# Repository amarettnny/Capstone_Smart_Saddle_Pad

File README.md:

# Capstone_Smart_Saddle_Pad

## Setting up ESP-IDF for the first time

- This folder, along with its subfolders, contains the firmware that runs on the ESP32 microcontrollers using ESP-IDF. In order to compile and flash our ESP-IDF projects, you need to do the following:

    - Install the ESP-IDF extension on VS Code, and follow the ESP-IDF Setup to install the latest version of ESP-IDF (default parameters should be fine)
    - Open up the root folder of the ESP-IDF project in VS Code
    - Set the correct COM port, microcontroller, and ESP-IDF on the bottom left if necessary
    - Common Compilation Issues:
        - Make sure that the .vscode directory in the root folder of your project has a c_cpp_properties.json, launch.json, and a settings.json. If it is missing any of those, delete the .vscode folder, and have ESP-IDF generate it using the [Add .vscode subdirectoy files] button found by clicking on the ESP-IDF Explorer Icon in the Activity Bar and looking under Advanced.
        - Also see if deleting the build directory and rebuilding works as well.
        - Make sure that you configured the SDK to have the size of flash be 8MB for the XIAO ESP32C5. (change 2MB to 8 MB in CONFIG_ESPTOOLPY_FLASHSIZE_2MB=y)

- **Linux & MacOS: (OPTIONAL)**
    - Set up an alias to execute export.sh.
    - To locate your shell profile, run the following command:
      ```
      echo $Shell
      ```
    - for MacOS it should show:
      ```
      /bin/zsh
      ```
    - If so, then navigate to *~/.zshrc*, then copy-paste the alias code on the documentation (replace *esp-idf* with your directory name (should be *esp-idf-v5.5.2*))
    - When you create a new terminal, it will automatically use *~/.zshrc* to set environment variables. (Can also do ```source ~/.zshrc``` to re-run those variables)
    - Currently (as of 1/28/26): when you navigate to the esp-idf project, in your terminal, you will have to re-run:
      ```
      get_idf
      ```
    - Then you will be able to do ```idf.py``` commands within your terminal. See the official ESP32 Guide for more commands: https://docs.espressif.com/projects/esp-idf/en/latest/esp32/get-started/linux-macos-start-project.html

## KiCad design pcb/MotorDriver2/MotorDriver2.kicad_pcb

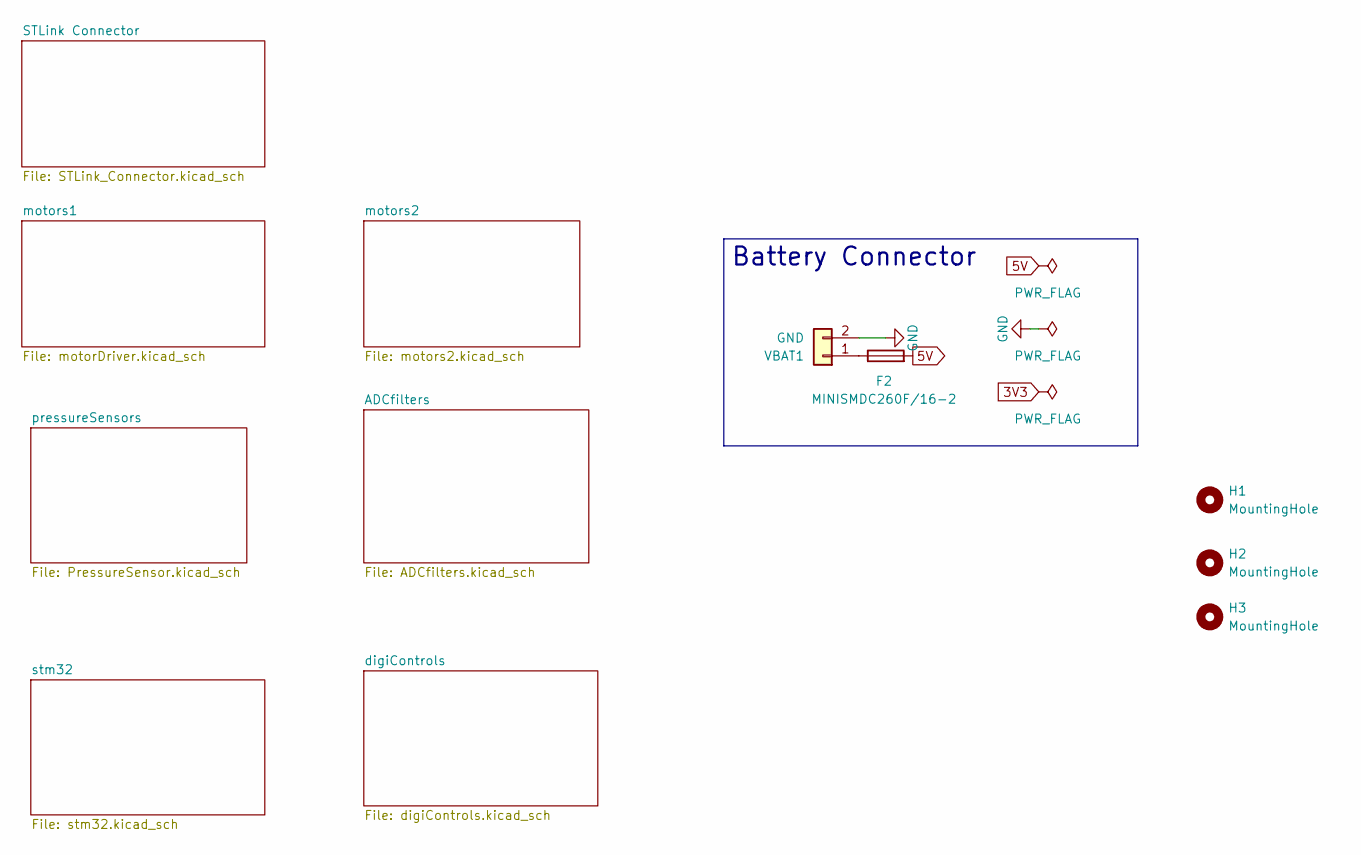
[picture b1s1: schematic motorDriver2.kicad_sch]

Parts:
F2: MINISMDC260F/16-2; Fuse_1812_4532Metric; LCSC C16490
H1, H2, H3: MountingHole; ToolingHole_1.152mm
VBAT1: GND; PinHeader_1x02_P2.54mm_Vertical

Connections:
5V: F2.2; also elsewhere on the board
GND: VBAT1.2; also elsewhere on the board
unnamed: F2.1, VBAT1.1

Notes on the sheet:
Battery Connector

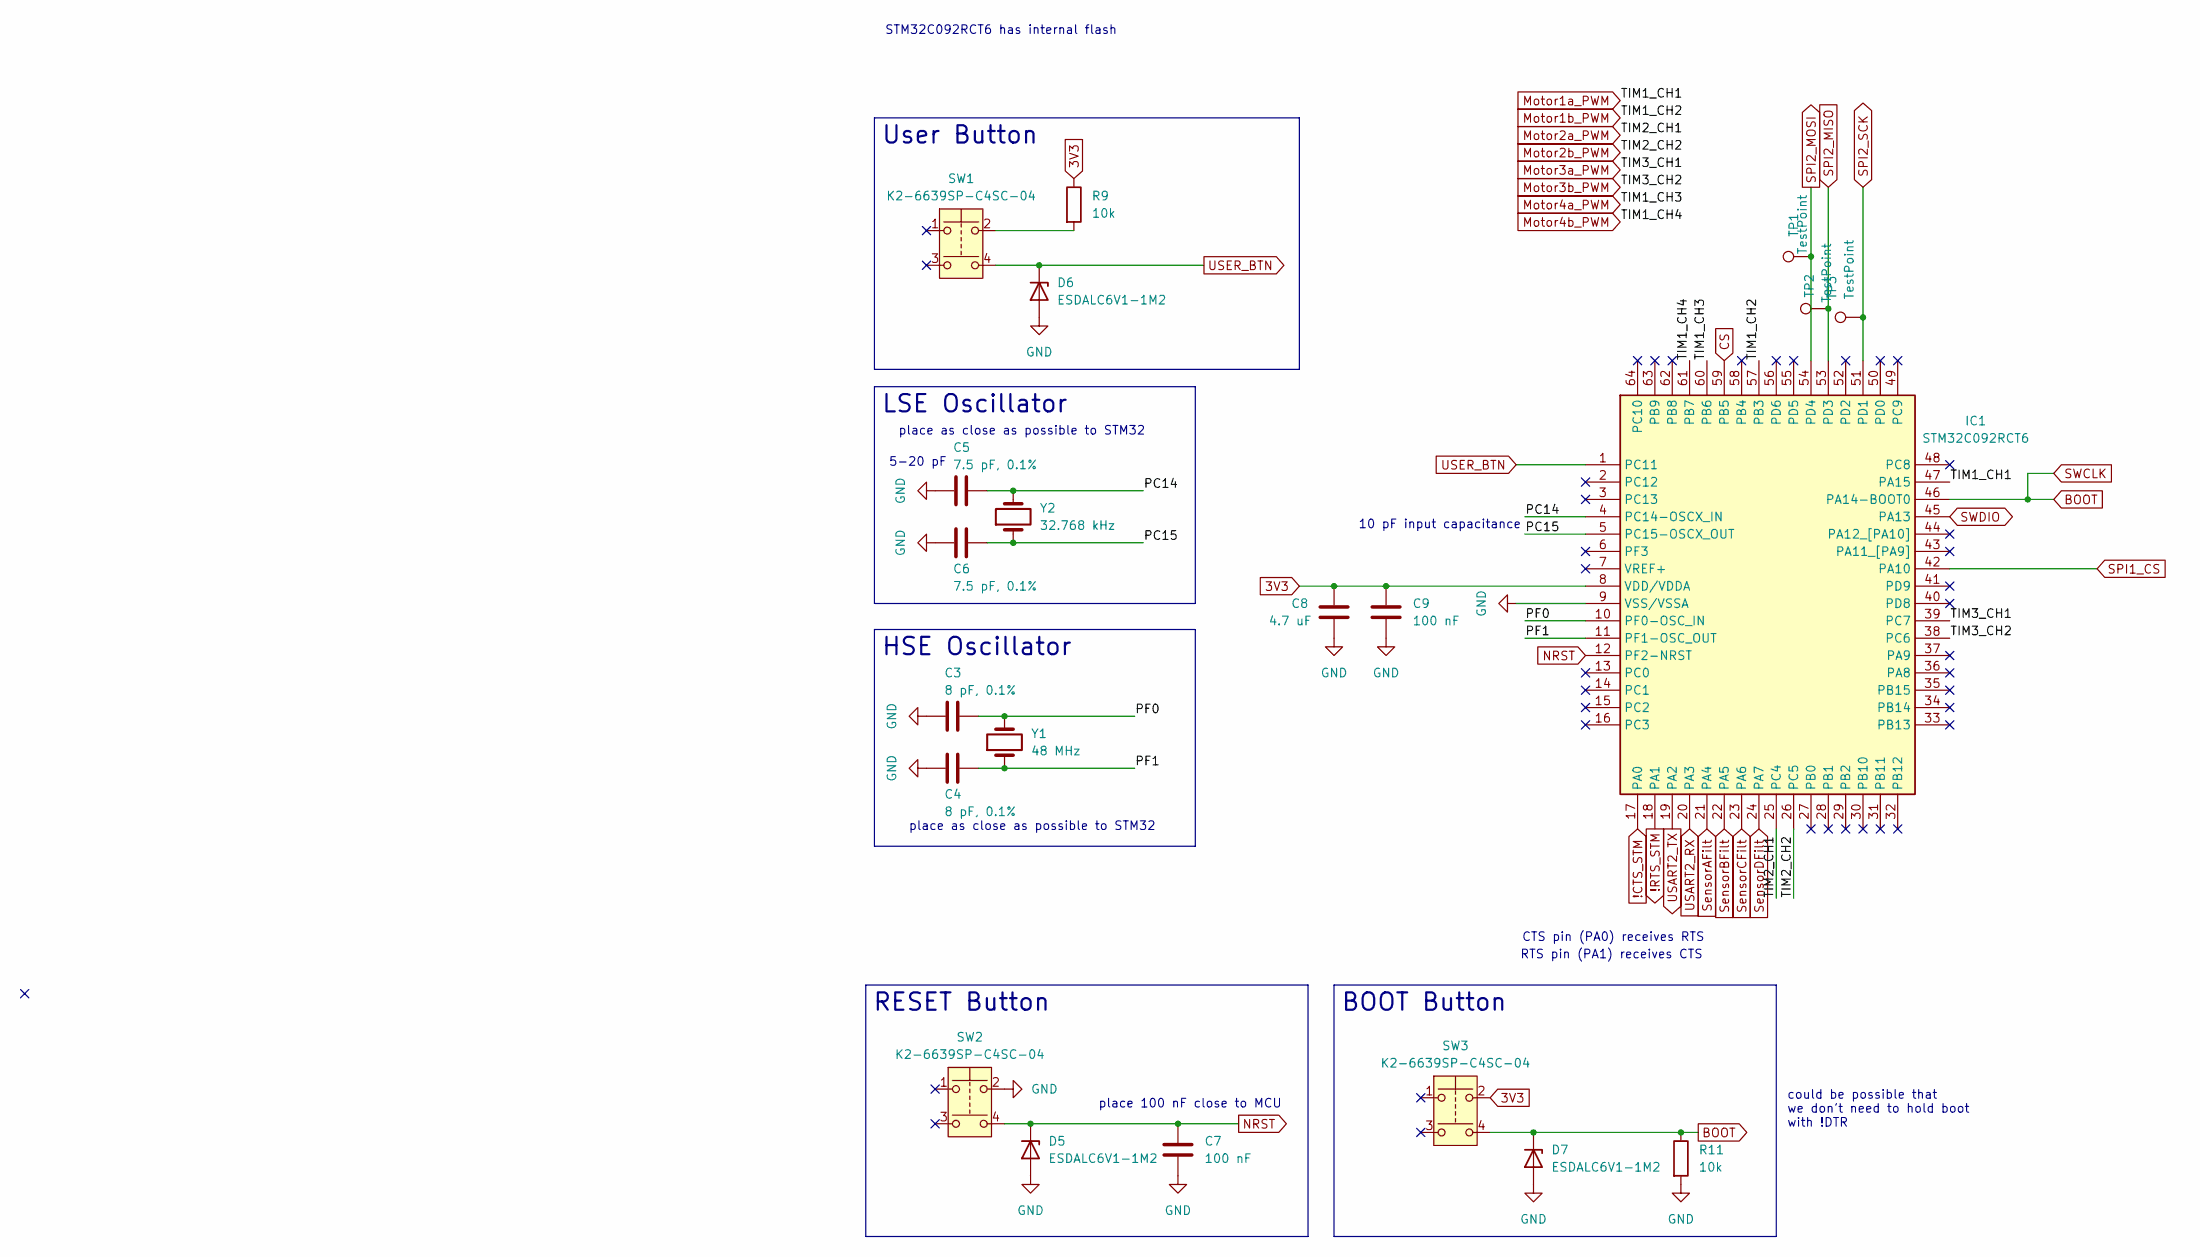
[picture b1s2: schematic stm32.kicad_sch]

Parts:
C3: 8 pF, 0.1%; C_0402_1005Metric; LCSC C3849295
C4: 8 pF, 0.1%; C_0402_1005Metric
C5, C6: 7.5 pF, 0.1%; C_0402_1005Metric; LCSC C161334
C7: 100 nF; C_0402_1005Metric; LCSC C1525
C8: 4.7 uF; C_0603_1608Metric; LCSC C19666
C9: 100 nF; C_0402_1005Metric
D5: ESDALC6V1-1M2; D_0402_1005Metric; LCSC C2649894
D6, D7: ESDALC6V1-1M2; D_0402_1005Metric
IC1: STM32C092RCT6; QFP50P1200X1200X160-64N; Manufacturer_Part_Number STM32C092RCT6; Mouser Part Number 511-STM32C092RCT6
R9, R11: 10k; R_0402_1005Metric
SW1, SW2, SW3: K2-6639SP-C4SC-04
TP1, TP2, TP3: TestPoint; TestPoint_Pad_1.0x1.0mm
Y1: 48 MHz; ECS-480-8-30-JGN-TR
Y2: 32.768 kHz; MU00527-32.768K

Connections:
3V3: C8.2, C9.1, IC1.8 (VDD/VDDA), R9.1, SW3.2; also elsewhere on the board
!CTS_STM: IC1.17 (PA0); also elsewhere on the board
!RTS_STM: IC1.18 (PA1); also elsewhere on the board
/stm32/PC14: C5.2, IC1.4 (PC14-OSCX_IN), Y2.2
/stm32/PC15: C6.1, IC1.5 (PC15-OSCX_OUT), Y2.1
/stm32/PF0: C3.2, IC1.10 (PF0-OSC_IN), Y1.2
/stm32/PF1: C4.1, IC1.11 (PF1-OSC_OUT), Y1.1
BOOT: D7.1 (K), IC1.46 (PA14-BOOT0), R11.1, SW3.4; also elsewhere on the board
CS: IC1.59 (PB5); also elsewhere on the board
GND: C3.1, C4.2, C5.1, C6.2, C7.2, C8.1, C9.2, D5.2 (A), D6.2 (A), D7.2 (A), IC1.9 (VSS/VSSA), R11.2, SW2.2; also elsewhere on the board
Motor1a_PWM: IC1.47 (PA15); also elsewhere on the board
Motor1b_PWM: IC1.57 (PB3); also elsewhere on the board
Motor2a_PWM: IC1.25 (PC4); also elsewhere on the board
Motor2b_PWM: IC1.26 (PC5); also elsewhere on the board
Motor3a_PWM: IC1.39 (PC7); also elsewhere on the board
Motor3b_PWM: IC1.38 (PC6); also elsewhere on the board
Motor4a_PWM: IC1.60 (PB6); also elsewhere on the board
Motor4b_PWM: IC1.61 (PB7); also elsewhere on the board
NRST: C7.1, D5.1 (K), IC1.12 (PF2-NRST), SW2.4
unnamed: R9.2, SW1.2
SPI1_CS: IC1.42 (PA10)
SPI2_MISO: IC1.53 (PD3), TP2.1; also elsewhere on the board
SPI2_MOSI: IC1.54 (PD4), TP1.1; also elsewhere on the board
SPI2_SCK: IC1.51 (PD1), TP3.1; also elsewhere on the board
SWDIO: IC1.45 (PA13); also elsewhere on the board
SensorAFilt: IC1.21 (PA4); also elsewhere on the board
SensorBFilt: IC1.22 (PA5); also elsewhere on the board
SensorCFilt: IC1.23 (PA6); also elsewhere on the board
SensorDFilt: IC1.24 (PA7); also elsewhere on the board
USART2_RX: IC1.20 (PA3); also elsewhere on the board
USART2_TX: IC1.19 (PA2); also elsewhere on the board
USER_BTN: D6.1 (K), IC1.1 (PC11), SW1.4

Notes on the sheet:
CTS pin (PA0) receives RTS
10 pF input capacitance
place as close as possible to STM32
5-20 pF
STM32C092RCT6 has internal flash
place 100 nF close to MCU
could be possible that we don't need to hold boot with !DTR
RTS pin (PA1) receives CTS
RESET Button
User Button
BOOT Button
HSE Oscillator
LSE Oscillator

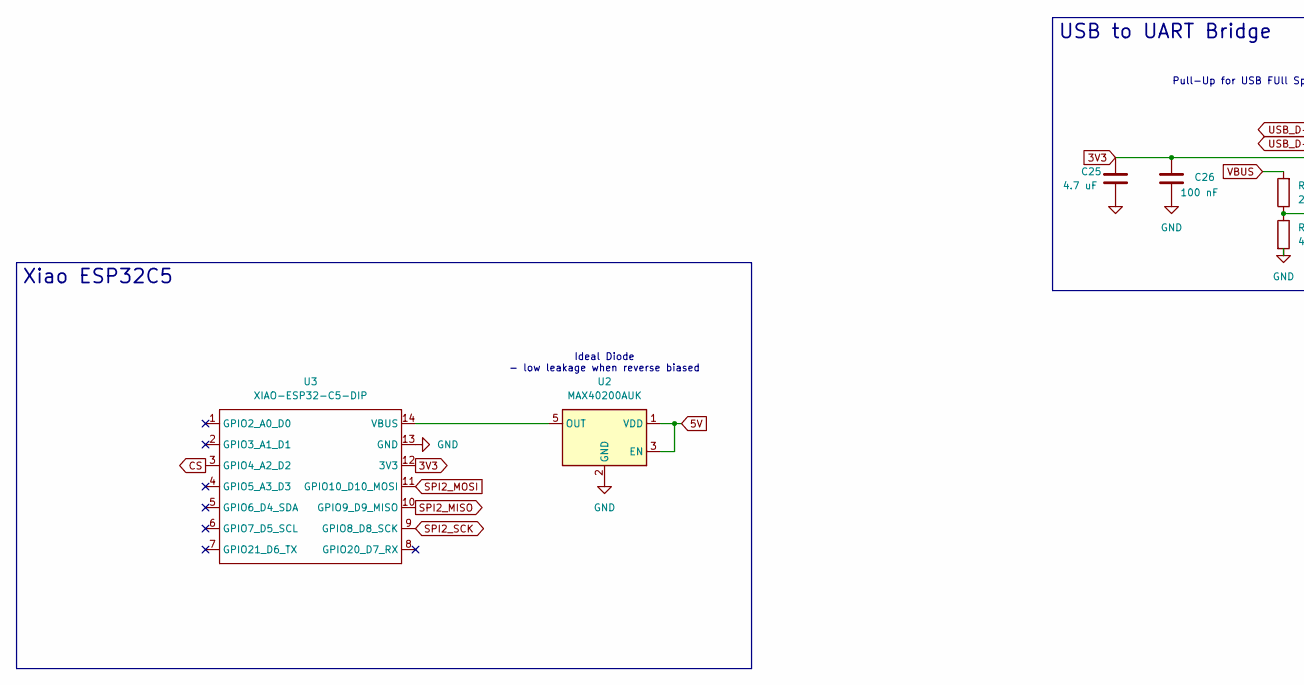
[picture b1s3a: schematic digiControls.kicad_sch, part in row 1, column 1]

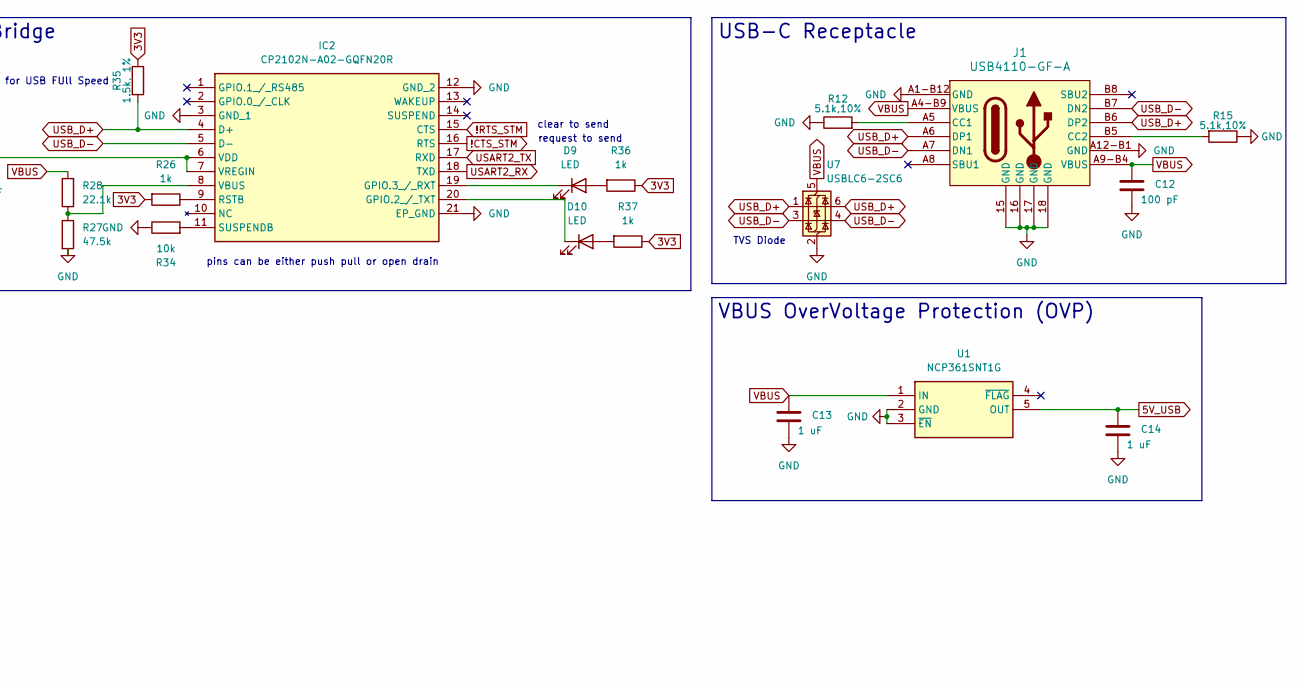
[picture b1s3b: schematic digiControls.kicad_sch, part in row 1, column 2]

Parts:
C12: 100 pF; C_0402_1005Metric
C13, C14: 1 uF; C_0603_1608Metric; LCSC C15849
C25: 4.7 uF; C_0603_1608Metric
C26: 100 nF; C_0402_1005Metric
D9, D10: LED; D_0402_1005Metric
IC2: CP2102N-A02-GQFN20R; CP2102NA02GQFN20; Mouser Part Number 634-CP2102NA02QFN20R
J1: USB4110-GF-A; USB4110-GF-A_GCT
R12, R15: 5.1k,10%; R_0402_1005Metric; LCSC C25905
R26, R36, R37: 1k; R_0402_1005Metric
R27: 47.5k; R_0402_1005Metric
R28: 22.1k; R_0402_1005Metric
R34: 10k; R_0402_1005Metric
R35: 1.5k, 1%; R_0402_1005Metric
U1: NCP361SNT1G; SOT95P275X110-5N; Mouser Part Number 863-NCP361SNT1G
U2: MAX40200AUK; SOT-23-5
U3: XIAO-ESP32-C5-DIP
U7: USBLC6-2SC6; SOT-23-6

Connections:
3V3: C25.2, C26.2, IC2.6 (VDD), IC2.7 (VREGIN), R26.2, R35.1, R36.1, R37.1, U3.12 (3V3); also elsewhere on the board
5V: U2.1 (VDD), U2.3 (EN); also elsewhere on the board
5V_USB: C14.2, U1.5 (OUT)
!CTS_STM: IC2.16 (RTS); also elsewhere on the board
!RTS_STM: IC2.15 (CTS); also elsewhere on the board
CS: U3.3 (GPIO4_A2_D2); also elsewhere on the board
GND: C12.1, C13.1, C14.1, C25.1, C26.1, IC2.3 (GND_1), IC2.12 (GND_2), IC2.21 (EP_GND), J1.15 (GND), J1.16 (GND), J1.17 (GND), J1.18 (GND), J1.A1-B12 (GND), J1.A12-B1 (GND), R12.1, R15.1, R27.2, R34.1, U1.2 (GND), U1.3 (~EN), U2.2 (GND), U3.13 (GND), U7.2 (GND); also elsewhere on the board
unnamed: D9.2 (A), R36.2
unnamed: D9.1 (K), IC2.19 (GPIO.3_/_RXT)
unnamed: D10.2 (A), R37.2
unnamed: D10.1 (K), IC2.20 (GPIO.2_/_TXT)
unnamed: IC2.9 (RSTB), R26.1
unnamed: IC2.11 (SUSPENDB), R34.2
unnamed: IC2.8 (VBUS), R27.1, R28.1
unnamed: J1.A5 (CC1), R12.2
unnamed: J1.B5 (CC2), R15.2
unnamed: U2.5 (OUT), U3.14 (VBUS)
SPI2_MISO: U3.10 (GPIO9_D9_MISO); also elsewhere on the board
SPI2_MOSI: U3.11 (GPIO10_D10_MOSI); also elsewhere on the board
SPI2_SCK: U3.9 (GPIO8_D8_SCK); also elsewhere on the board
USART2_RX: IC2.18 (TXD); also elsewhere on the board
USART2_TX: IC2.17 (RXD); also elsewhere on the board
USB_D+: IC2.4 (D+), J1.A6 (DP1), J1.B6 (DP2), R35.2, U7.1 (I/O1), U7.6 (I/O1)
USB_D-: IC2.5 (D-), J1.A7 (DN1), J1.B7 (DN2), U7.3 (I/O2), U7.4 (I/O2)
VBUS: C12.2, C13.2, J1.A4-B9 (VBUS), J1.A9-B4 (VBUS), R28.2, U1.1 (IN), U7.5 (VBUS)

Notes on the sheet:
TVS Diode
request to send
Ideal Diode - low leakage when reverse biased
pins can be either push pull or open drain
clear to send
Pull-Up for USB FUll Speed
VBUS OverVoltage Protection (OVP)
USB to UART Bridge
Xiao ESP32C5
USB-C Receptacle

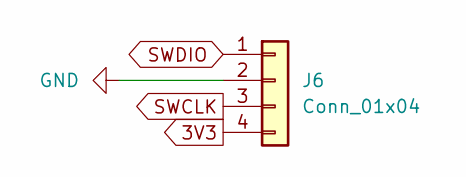
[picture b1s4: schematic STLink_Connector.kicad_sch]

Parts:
J6: Conn_01x04; PinHeader_1x04_P2.54mm_Vertical

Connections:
3V3: J6.4; also elsewhere on the board
BOOT: J6.3; also elsewhere on the board
GND: J6.2; also elsewhere on the board
SWDIO: J6.1; also elsewhere on the board

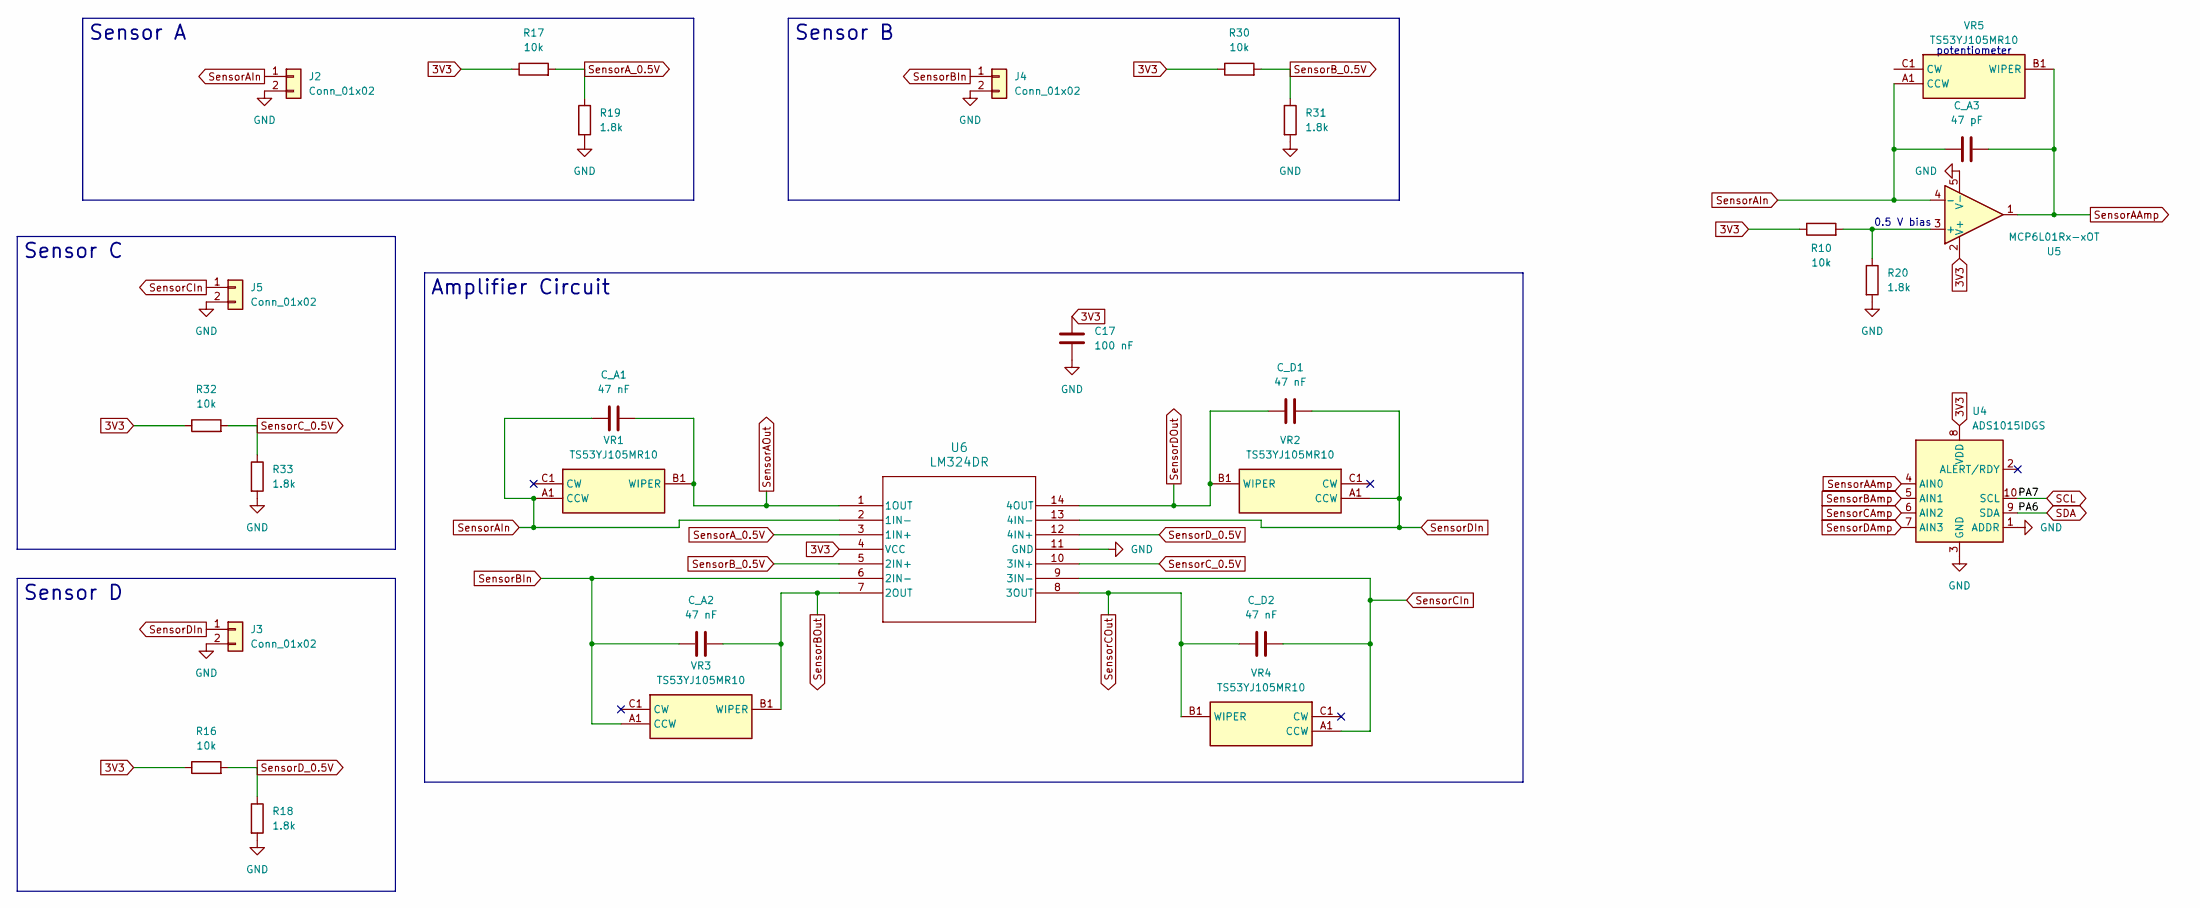
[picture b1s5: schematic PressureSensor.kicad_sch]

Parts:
C17: 100 nF; C_0402_1005Metric
C_A1: 47 nF; C_0402_1005Metric; LCSC C77012
C_A2: 47 nF; C_0402_1005Metric
C_A3: 47 pF; C_0402_1005Metric; LCSC C77012
C_D1, C_D2: 47 nF; C_0402_1005Metric
J2, J3, J4, J5: Conn_01x02; PinHeader_1x02_P2.54mm_Vertical
R10, R16, R17, R30, R32: 10k; R_0402_1005Metric
R18, R19: 1.8k; R_0402_1005Metric; LCSC C25871
R20, R31, R33: 1.8k; R_0402_1005Metric
U4: ADS1015IDGS; TSSOP-10_3x3mm_P0.5mm
U5: MCP6L01Rx-xOT; SOT-23-5
U6: LM324DR; D14
VR1, VR2, VR3, VR4, VR5: TS53YJ105MR10; Mouser Part Number 72-TS53YJ-1M

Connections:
3V3: C17.1, R10.1, R16.1, R17.1, R30.1, R32.1, U4.8 (VDD), U5.2 (V+), U6.4 (VCC); also elsewhere on the board
GND: C17.2, J2.2, J3.2, J4.2, J5.2, R18.2, R19.2, R20.2, R31.2, R33.2, U4.1 (ADDR), U4.3 (GND), U5.5 (V-), U6.11 (GND); also elsewhere on the board
unnamed: C_A3.1, U4.4 (AIN0), U5.1, VR5.B1 (WIPER)
unnamed: R10.2, R20.1, U5.3 (+)
SensorAIn: C_A1.2, C_A3.2, J2.1, U5.4 (-), U6.2 (1IN-), VR1.A1 (CCW), VR5.A1 (CCW)
SensorAOut: C_A1.1, U6.1 (1OUT), VR1.B1 (WIPER); also elsewhere on the board
SensorA_0.5V: R17.2, R19.1, U6.3 (1IN+)
SensorBIn: C_A2.2, J4.1, U6.6 (2IN-), VR3.A1 (CCW)
SensorBOut: C_A2.1, U6.7 (2OUT), VR3.B1 (WIPER); also elsewhere on the board
SensorB_0.5V: R30.2, R31.1, U6.5 (2IN+)
SensorCIn: C_D2.1, J5.1, U6.9 (3IN-), VR4.A1 (CCW)
SensorCOut: C_D2.2, U6.8 (3OUT), VR4.B1 (WIPER); also elsewhere on the board
SensorC_0.5V: R32.2, R33.1, U6.10 (3IN+)
SensorDIn: C_D1.1, J3.1, U6.13 (4IN-), VR2.A1 (CCW)
SensorDOut: C_D1.2, U6.14 (4OUT), VR2.B1 (WIPER); also elsewhere on the board
SensorD_0.5V: R16.2, R18.1, U6.12 (4IN+)

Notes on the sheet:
potentiometer
0.5 V bias
Amplifier Circuit
Sensor B
Sensor D
Sensor C
Sensor A

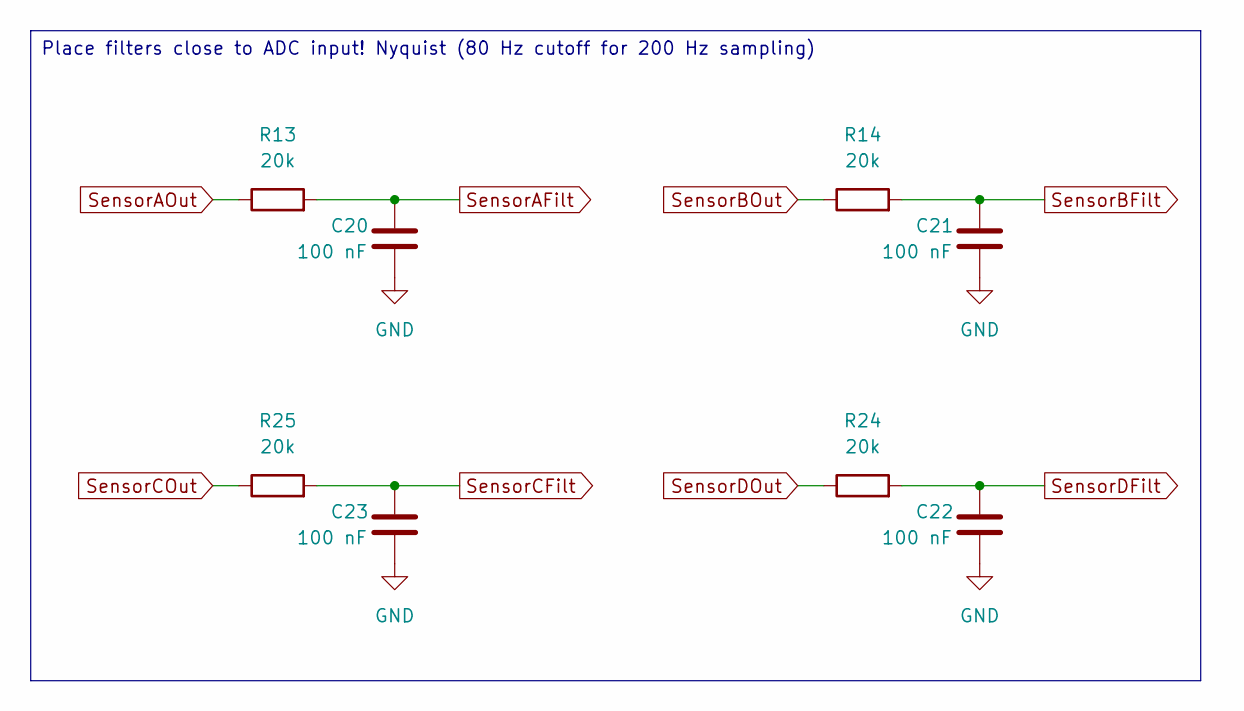
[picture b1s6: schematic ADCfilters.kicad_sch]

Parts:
C20, C21, C22, C23: 100 nF; C_0402_1005Metric
R13, R14, R24, R25: 20k; R_0402_1005Metric

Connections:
GND: C20.1, C21.1, C22.1, C23.1; also elsewhere on the board
SensorAFilt: C20.2, R13.2; also elsewhere on the board
SensorAOut: R13.1; also elsewhere on the board
SensorBFilt: C21.2, R14.2; also elsewhere on the board
SensorBOut: R14.1; also elsewhere on the board
SensorCFilt: C23.2, R25.2; also elsewhere on the board
SensorCOut: R25.1; also elsewhere on the board
SensorDFilt: C22.2, R24.2; also elsewhere on the board
SensorDOut: R24.1; also elsewhere on the board

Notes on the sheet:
Place filters close to ADC input! Nyquist (80 Hz cutoff for 200 Hz sampling)

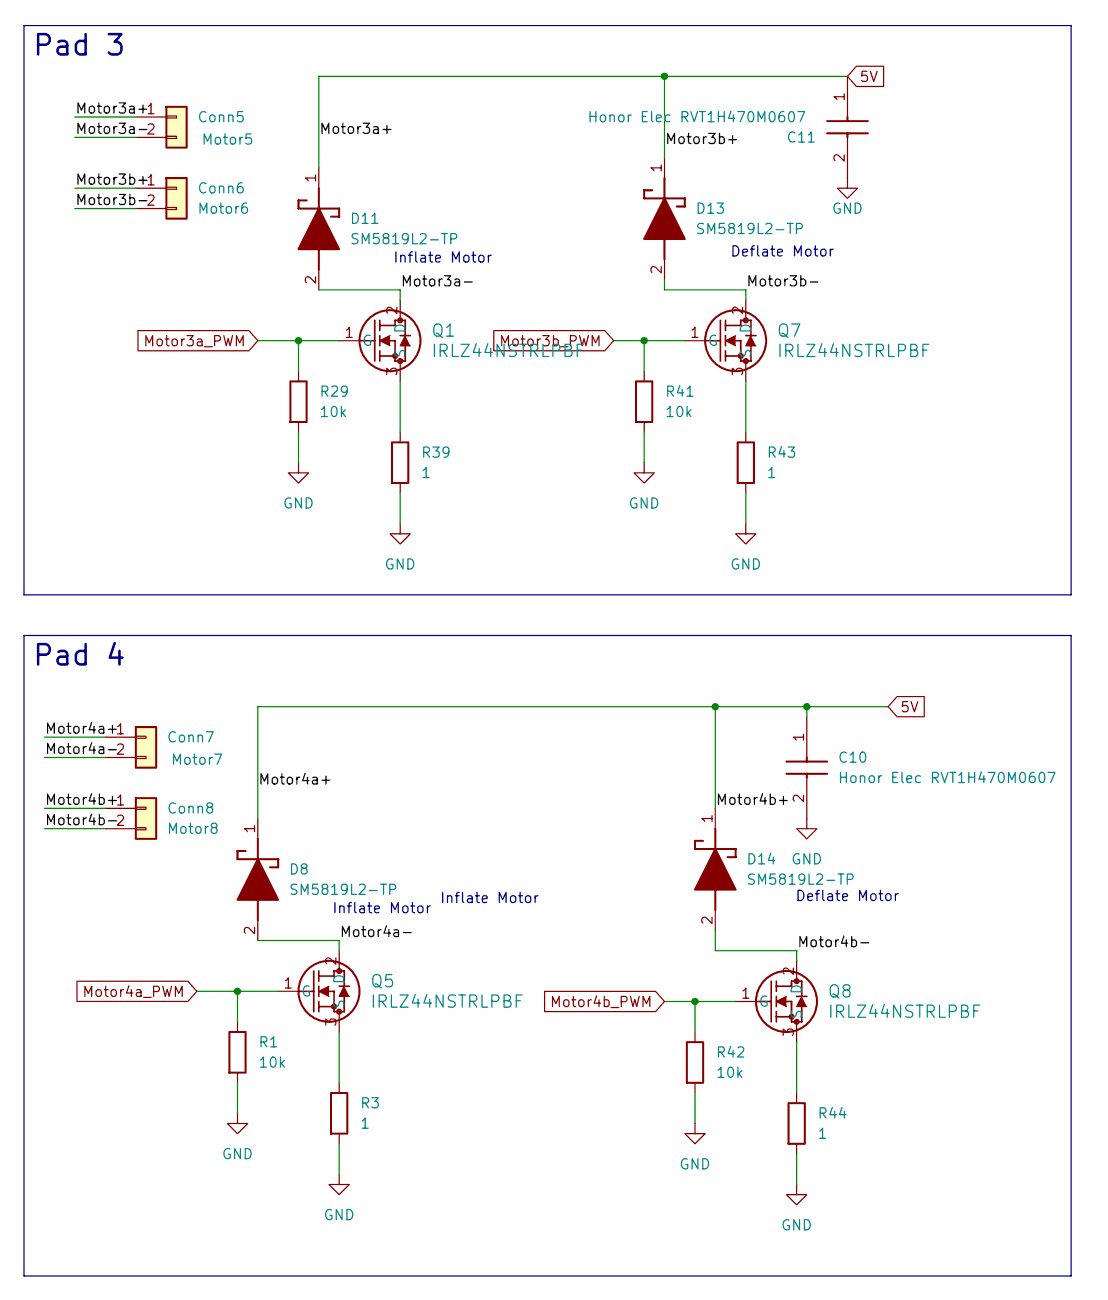
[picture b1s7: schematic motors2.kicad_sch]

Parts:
C10, C11: Honor Elec RVT1H470M0607; CAPAE680X800N; Manufacturer_Part_Number MAL214297108E3
Conn5: Motor5; PinHeader_1x02_P2.54mm_Vertical
Conn6: Motor6; PinHeader_1x02_P2.54mm_Vertical
Conn7: Motor7; PinHeader_1x02_P2.54mm_Vertical
Conn8: Motor8; PinHeader_1x02_P2.54mm_Vertical
D8, D11, D13, D14: SM5819L2-TP; SDO_SM5819L2-TP_MCE; Mouser Part Number 833-SM5819L2-TP
Q1, Q5, Q7, Q8: IRLZ44NSTRLPBF; NMOSGDS_D2PAK_INF
R1: 10k; R_0402_1005Metric; LCSC C25744
R3: 1; R_1206_3216Metric; LCSC C17928
R29, R41, R42: 10k; R_0402_1005Metric
R39, R43, R44: 1; R_1206_3216Metric

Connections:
5V: C10.1 (+), C11.1 (+), Conn5.1, Conn6.1, Conn7.1, Conn8.1, D8.1 (K), D11.1 (K), D13.1 (K), D14.1 (K); also elsewhere on the board
/motors2/Motor3a-: Conn5.2, D11.2 (A), Q1.2 (D)
/motors2/Motor3b-: Conn6.2, D13.2 (A), Q7.2 (D)
/motors2/Motor4a-: Conn7.2, D8.2 (A), Q5.2 (D)
/motors2/Motor4b-: Conn8.2, D14.2 (A), Q8.2 (D)
GND: C10.2 (-), C11.2 (-), R1.2, R3.2, R29.2, R39.2, R41.2, R42.2, R43.2, R44.2; also elsewhere on the board
Motor3a_PWM: Q1.1 (G), R29.1; also elsewhere on the board
Motor3b_PWM: Q7.1 (G), R41.1; also elsewhere on the board
Motor4a_PWM: Q5.1 (G), R1.1; also elsewhere on the board
Motor4b_PWM: Q8.1 (G), R42.1; also elsewhere on the board
unnamed: Q1.3 (S), R39.1
unnamed: Q5.3 (S), R3.1
unnamed: Q7.3 (S), R43.1
unnamed: Q8.3 (S), R44.1

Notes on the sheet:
Inflate Motor
Deflate Motor
Pad 3
Pad 4

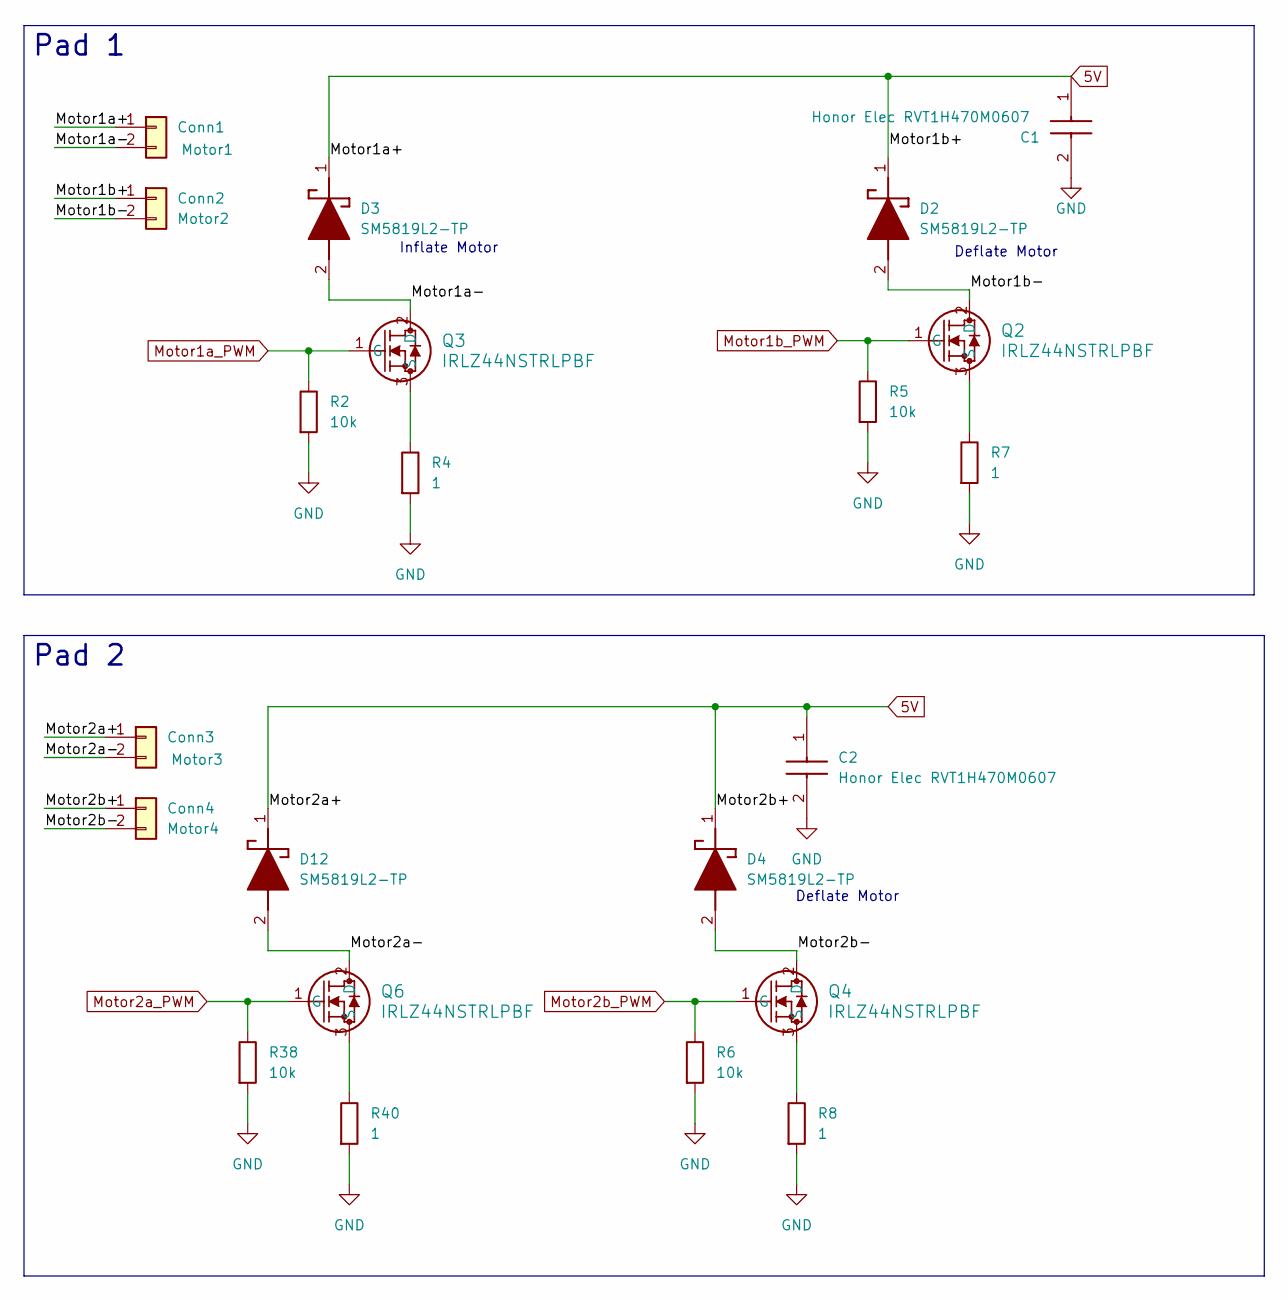
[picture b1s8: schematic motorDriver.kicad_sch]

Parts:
C1, C2: Honor Elec RVT1H470M0607; CAPAE680X800N; Manufacturer_Part_Number MAL214297108E3
Conn1: Motor1; PinHeader_1x02_P2.54mm_Vertical
Conn2: Motor2; PinHeader_1x02_P2.54mm_Vertical
Conn3: Motor3; PinHeader_1x02_P2.54mm_Vertical
Conn4: Motor4; PinHeader_1x02_P2.54mm_Vertical
D2, D3, D4, D12: SM5819L2-TP; SDO_SM5819L2-TP_MCE; Mouser Part Number 833-SM5819L2-TP
Q2, Q3, Q4, Q6: IRLZ44NSTRLPBF; NMOSGDS_D2PAK_INF
R2, R5, R6, R38: 10k; R_0402_1005Metric
R4, R7, R8: 1; R_1206_3216Metric; LCSC C17928
R40: 1; R_1206_3216Metric

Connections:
5V: C1.1 (+), C2.1 (+), Conn1.1, Conn2.1, Conn3.1, Conn4.1, D2.1 (K), D3.1 (K), D4.1 (K), D12.1 (K); also elsewhere on the board
/motors1/Motor1a-: Conn1.2, D3.2 (A), Q3.2 (D)
/motors1/Motor1b-: Conn2.2, D2.2 (A), Q2.2 (D)
/motors1/Motor2a-: Conn3.2, D12.2 (A), Q6.2 (D)
/motors1/Motor2b-: Conn4.2, D4.2 (A), Q4.2 (D)
GND: C1.2 (-), C2.2 (-), R2.2, R4.2, R5.2, R6.2, R7.2, R8.2, R38.2, R40.2; also elsewhere on the board
Motor1a_PWM: Q3.1 (G), R2.1; also elsewhere on the board
Motor1b_PWM: Q2.1 (G), R5.1; also elsewhere on the board
Motor2a_PWM: Q6.1 (G), R38.1; also elsewhere on the board
Motor2b_PWM: Q4.1 (G), R6.1; also elsewhere on the board
unnamed: Q2.3 (S), R7.1
unnamed: Q3.3 (S), R4.1
unnamed: Q4.3 (S), R8.1
unnamed: Q6.3 (S), R40.1

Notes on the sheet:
Deflate Motor
Inflate Motor
Pad 1
Pad 2
